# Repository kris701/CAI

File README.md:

# Centralised Auxiliary Interface (CAI)

A project about centralizing a lot of the auxiliary systems for my 3D printer.
As well as add some new systems, like auto-screws, that makes the operation of the printer a lot easier!
It is also designed to be mounted on my [toolhead extension project](https://github.com/kris701/SnapMaker-Toolhead-Extensions).

### Auto-Screws
Automatic screws to take heatbed and toolhead off and on, to make it significantly easier to switch between CNC, Laser engraver and 3D-printer!

### Menu System
Easy to modify menu system, with a rotary push button control.

### Auto-Setup
Single menu item, to setup all thats needed for CNC or 3D print.
Consisting of tightening screws, turning on LED and for 3D printing, turn on the nozzle blower.

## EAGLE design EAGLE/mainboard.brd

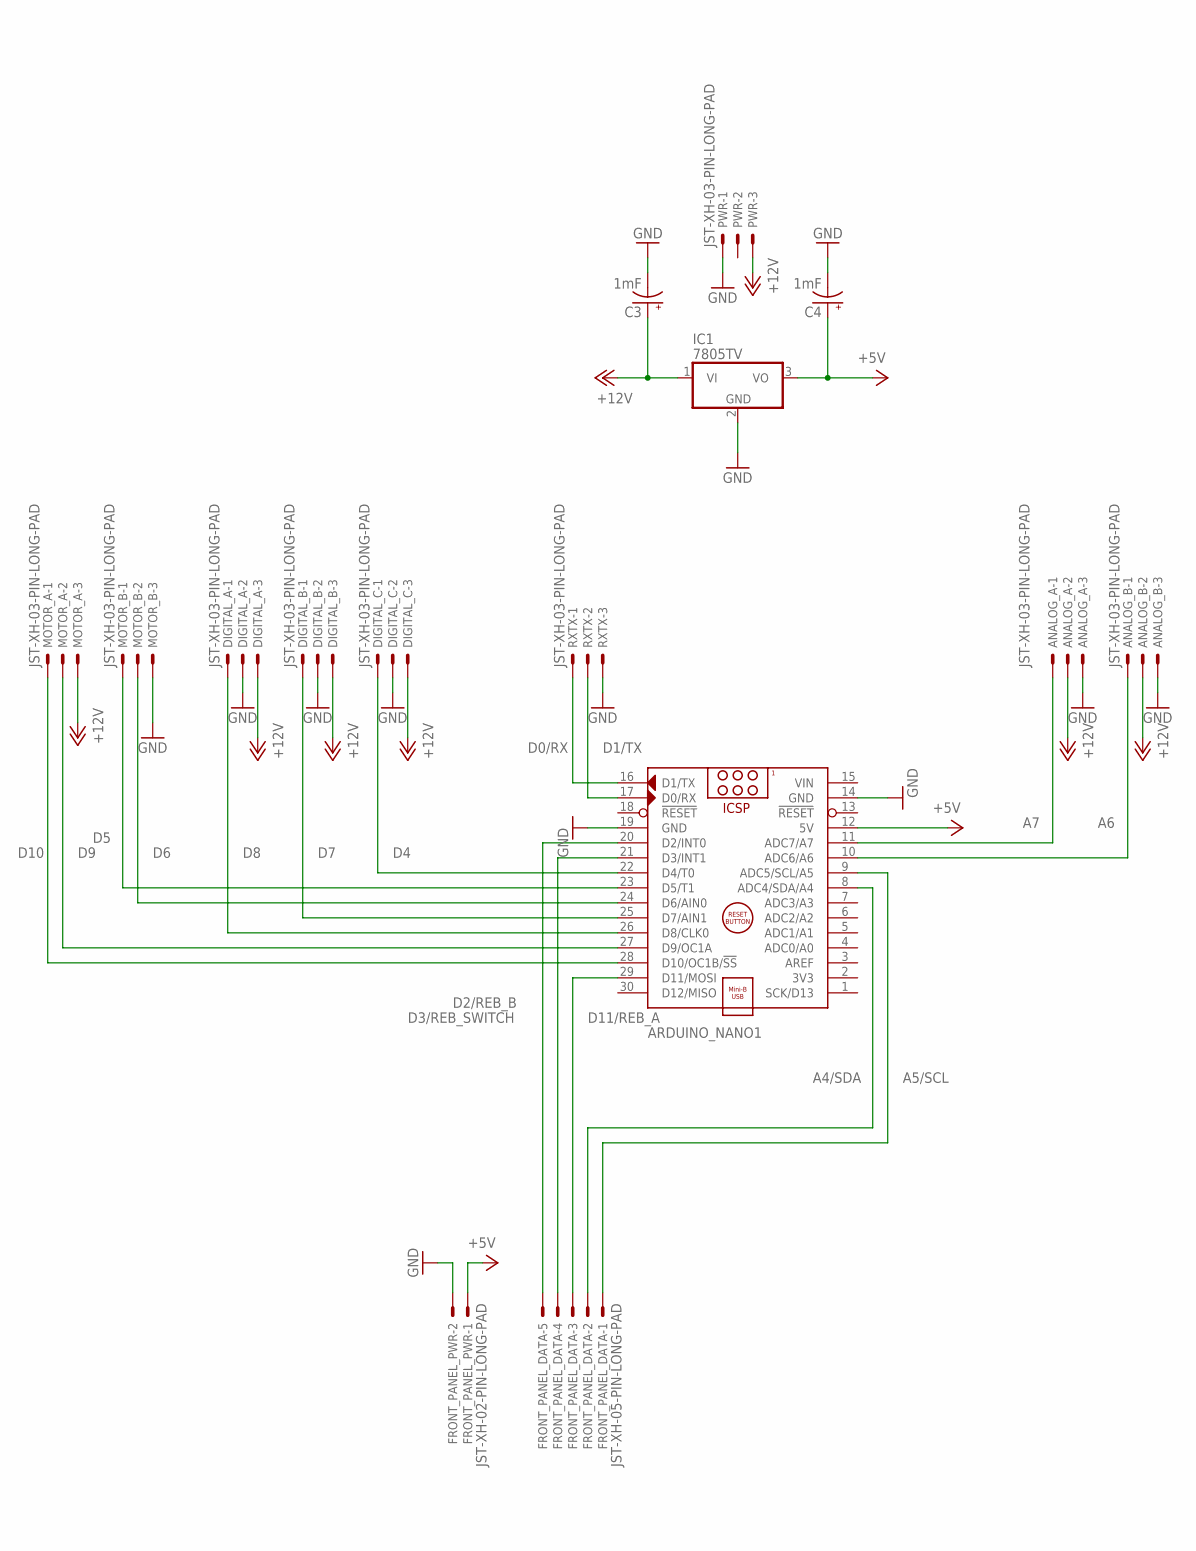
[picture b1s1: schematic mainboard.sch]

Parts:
ANALOG_A: JST-XH-03-PIN-LONG-PAD; JST-XH-03-PACKAGE-LONG-PAD
ANALOG_B: JST-XH-03-PIN-LONG-PAD; JST-XH-03-PACKAGE-LONG-PAD
ARDUINO_NANO1: ARDUINO_NANO
C3, C4: 1mF; CPOL-RADIAL-5MM-10MM
DIGITAL_A: JST-XH-03-PIN-LONG-PAD; JST-XH-03-PACKAGE-LONG-PAD
DIGITAL_B: JST-XH-03-PIN-LONG-PAD; JST-XH-03-PACKAGE-LONG-PAD
DIGITAL_C: JST-XH-03-PIN-LONG-PAD; JST-XH-03-PACKAGE-LONG-PAD
FRONT_PANEL_DATA: JST-XH-05-PIN-LONG-PAD; JST-XH-05-PACKAGE-LONG-PAD
FRONT_PANEL_PWR: JST-XH-02-PIN-LONG-PAD; JST-XH-02-PACKAGE-LONG-PAD
IC1: 7805TV; TO220V
MOTOR_A: JST-XH-03-PIN-LONG-PAD; JST-XH-03-PACKAGE-LONG-PAD
MOTOR_B: JST-XH-03-PIN-LONG-PAD; JST-XH-03-PACKAGE-LONG-PAD
PWR: JST-XH-03-PIN-LONG-PAD; JST-XH-03-PACKAGE-LONG-PAD
RXTX: JST-XH-03-PIN-LONG-PAD; JST-XH-03-PACKAGE-LONG-PAD

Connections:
+5V: ARDUINO_NANO1.12 (5V), C4.+, FRONT_PANEL_PWR.1, IC1.3 (VO)
+12V: ANALOG_A.2, ANALOG_B.2, C3.+, DIGITAL_A.3, DIGITAL_B.3, DIGITAL_C.3, IC1.1 (VI), MOTOR_A.3, PWR.3
A4/SDA: ARDUINO_NANO1.8 (ADC4/SDA/A4), FRONT_PANEL_DATA.2
A5/SCL: ARDUINO_NANO1.9 (ADC5/SCL/A5), FRONT_PANEL_DATA.1
A6: ANALOG_B.1, ARDUINO_NANO1.10 (ADC6/A6)
A7: ANALOG_A.1, ARDUINO_NANO1.11 (ADC7/A7)
D0/RX: ARDUINO_NANO1.17 (D0/RX), RXTX.2
D1/TX: ARDUINO_NANO1.16 (D1/TX), RXTX.1
D2/REB_B: ARDUINO_NANO1.20 (D2/INT0), FRONT_PANEL_DATA.5
D3/REB_SWITCH: ARDUINO_NANO1.21 (D3/INT1), FRONT_PANEL_DATA.4
D4: ARDUINO_NANO1.22 (D4/T0), DIGITAL_C.1
D5: ARDUINO_NANO1.23 (D5/T1), MOTOR_B.1
D6: ARDUINO_NANO1.24 (D6/AIN0), MOTOR_B.2
D7: ARDUINO_NANO1.25 (D7/AIN1), DIGITAL_B.1
D8: ARDUINO_NANO1.26 (D8/CLK0), DIGITAL_A.1
D9: ARDUINO_NANO1.27 (D9/OC1A), MOTOR_A.2
D10: ARDUINO_NANO1.28 (D10/OC1B/!SS), MOTOR_A.1
D11/REB_A: ARDUINO_NANO1.29 (D11/MOSI), FRONT_PANEL_DATA.3
GND: ANALOG_A.3, ANALOG_B.3, ARDUINO_NANO1.14 (GND), ARDUINO_NANO1.19 (GND), C3.-, C4.-, DIGITAL_A.2, DIGITAL_B.2, DIGITAL_C.2, FRONT_PANEL_PWR.2, IC1.2 (GND), MOTOR_B.3, PWR.1, RXTX.3
VIN: ARDUINO_NANO1.15 (VIN)

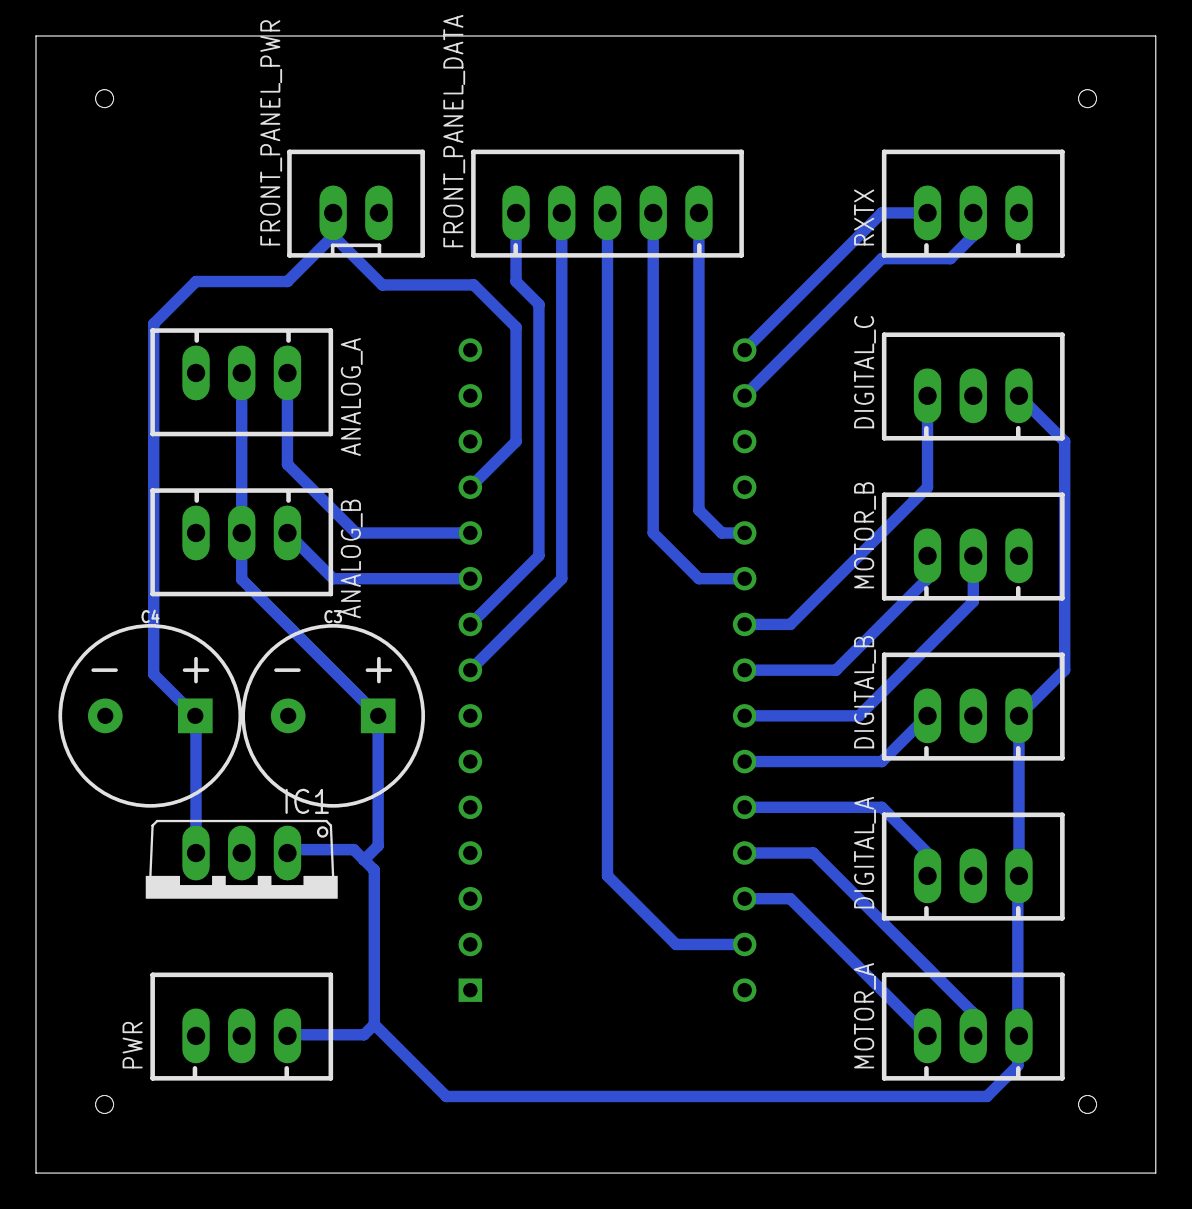
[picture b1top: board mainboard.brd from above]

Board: 2 copper layers, 62.2 x 63.2 mm, 15 parts (1 on the bottom side), 19 nets.

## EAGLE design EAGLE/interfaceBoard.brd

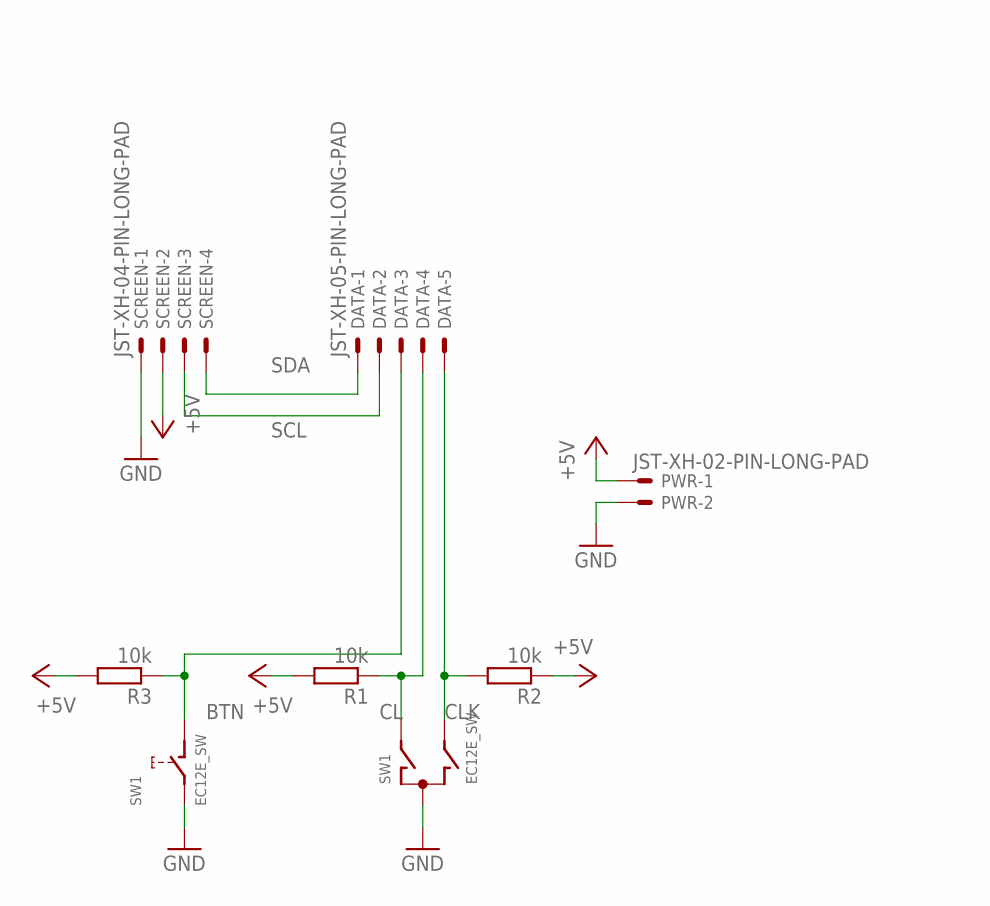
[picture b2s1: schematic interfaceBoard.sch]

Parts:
DATA: JST-XH-05-PIN-LONG-PAD; JST-XH-05-PACKAGE-LONG-PAD
PWR: JST-XH-02-PIN-LONG-PAD; JST-XH-02-PACKAGE-LONG-PAD
R1, R2, R3: 10k; 0204/7
SCREEN: JST-XH-04-PIN-LONG-PAD; JST-XH-04-PACKAGE-LONG-PAD
SW1: EC12E_SW; ALPS_EC12E_SW

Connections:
+5V: PWR.1, R1.2, R2.1, R3.2, SCREEN.2
BTN: DATA.3, R3.1, SW1.D (1)
CL: DATA.4, R1.1, SW1.A
CLK: DATA.5, R2.2, SW1.B
GND: PWR.2, SCREEN.1, SW1.C, SW1.E (2)
SCL: DATA.2, SCREEN.3
SDA: DATA.1, SCREEN.4

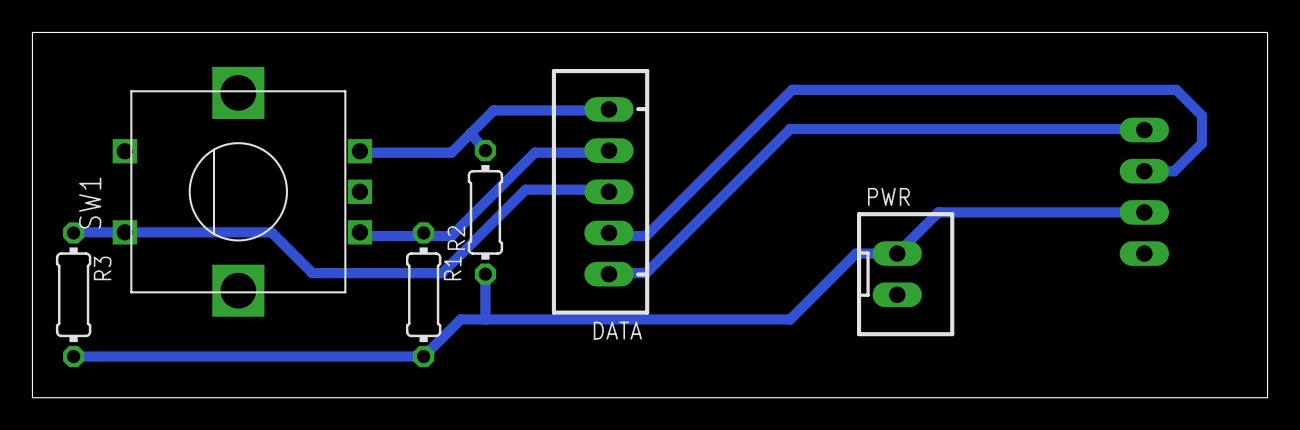
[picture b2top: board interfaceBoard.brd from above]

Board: 2 copper layers, 76.2 x 22.5 mm, 7 parts (1 on the bottom side), 7 nets.

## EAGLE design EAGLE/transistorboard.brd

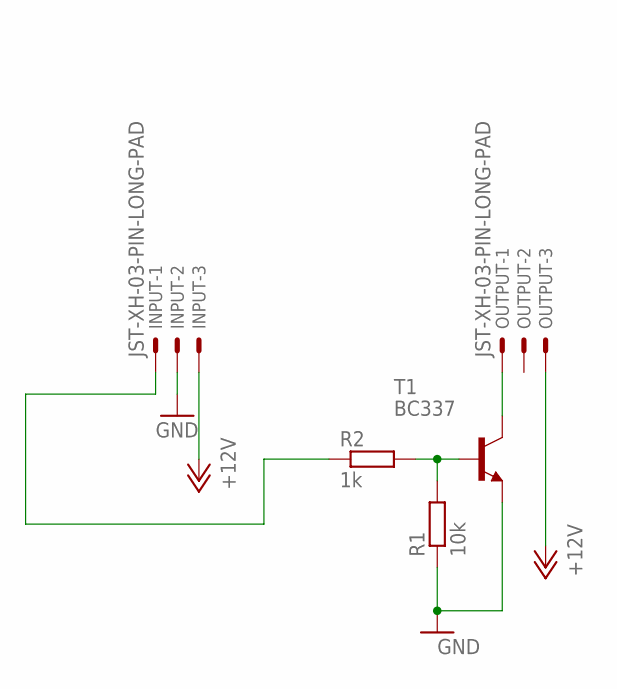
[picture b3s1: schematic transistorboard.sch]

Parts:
INPUT: JST-XH-03-PIN-LONG-PAD; JST-XH-03-PACKAGE-LONG-PAD
OUTPUT: JST-XH-03-PIN-LONG-PAD; JST-XH-03-PACKAGE-LONG-PAD
R1: 10k; 0204/7
R2: 1k; 0204/7
T1: BC337; TO92

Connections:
+12V: INPUT.3, OUTPUT.3
GND: INPUT.2, R1.1, T1.1 (E)
unnamed: OUTPUT.1, T1.3 (C)
unnamed: INPUT.1, R2.1
unnamed: R1.2, R2.2, T1.2 (B)

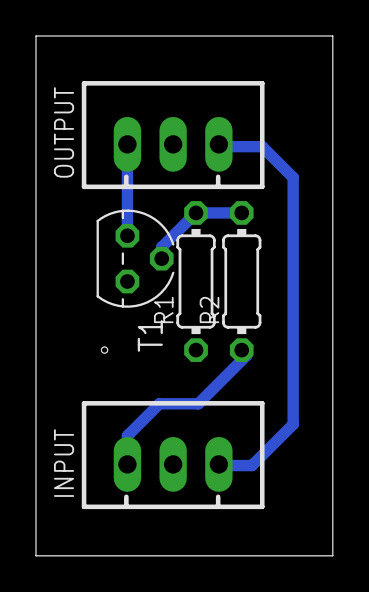
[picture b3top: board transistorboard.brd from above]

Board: 2 copper layers, 16.5 x 28.9 mm, 5 parts (0 on the bottom side), 5 nets.

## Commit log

2021-03-04 Add .gitignore and .gitattributes.
2021-03-04 Add project files.
2021-03-04 * Purged .ino file to default
2021-03-05 * got a basic menu structure to work
2021-03-05 * Removed `String` reference, and uses `const char*` instead
2021-03-05 * big purge * sub menus with sub menues possible * simpler to add new menu items
2021-03-05 * Split the program back out into some classes
2021-03-05 * Cleaned up * Added the systems needed to display text on the OLED screen * Added IO drivers for future modules
2021-03-05 * Removed unused files * Optimised some data types * Made a macro, to switch serial on and off
2021-03-05 * Did some cleanup
2021-03-05 * Added the board schematics for the PCB boards
2021-03-06 * Added definitions for available pins
2021-03-06 * Fixed issue #1 * Also added some more serial debugging
2021-03-08 * Saved a small bit of memory in the `menuTree`
2021-03-08 * Further reduced memory usage, with PROGMEM * Added some default text strings that can be used, such as "ON" and "OFF"
2021-03-08 * Added a delay in loop, so not to waste too much power
2021-03-08 * Made a lot of methods use constants instead
2021-03-08 * Added a lot of classes to be able to set things to private and public
2021-03-08 * Made more classification
2021-03-09 * Made a configuration section * Changed the DD designation in CAI.h to just numbers
2021-03-10 * Changed the rotary encoder code, to match that of the following source: - https://www.instructables.com/Tutorial-of-Rotary-Encoder-With-Arduino/ * Changed boards and schematic, so that interrupt pi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
2021-03-10 * Changed symbolic constants to fit mother board * Removed function pointers from the `RotaryButtonDriver` class, since they are not used * Added pinModes for all pins used for the Rotary Button
2021-03-10 * Made some minor changes on the motherboard, so that the +5v rail is connected to +5v on the arduino instead of vin
2021-03-10 * Optimised the motherboard a little
2021-03-10 * Added some "pseudo-properties" somewhat like C# with macros
2021-03-11 * Moved all EAGLE files into the project * Removed old copy-pasted boards * Updated .gitignore
2021-03-11 * Now gives a warning when compiling with SERIAL_PRINT to be true
2021-03-11 * Made some more work with properties * Made two classes in ModuleDrivers instead of just one * Fixed an issue, where the "SET" methods of properties didnt work * Made some initial checking on valid 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
2021-03-12 * Made some value checking * Also added a flag `SERIAL_DEBUG` to print errors that arrise from `Set` methods
2021-03-12 * Removed unused `this->` statements
2021-03-12 * Cleaned up and fixed the macro `CHECKVALUE`
2021-03-16 * Fixed code so it works with the SH1106 chip * Made initial menu work * Removed serial on warning * Now uses significantly less memory from new library
2021-03-16 * Updated some getters * Updated the intro screen
2021-03-17 * Made the entire screen refreshing sequence a lot more smooth * Added some more structured rectangle controls, to make it easier to allign items * Made a highlight animation when a button is clicked
2021-03-17 * Updated the `EnterMenu()` method * Removed unused define
2021-03-17 * Made the enter menu highlighting faster
2021-03-17 * Removed buffer
2021-03-17 * Removed the Get and Set structure
2021-03-17 * Did a lot of optimization of the menu rendering
2021-03-17 * Took care of issue #2 - Configuration of different systems have been put in a seperate file and header
2021-03-18 * Moved some constant values outside of the ScreenDriver class
2021-03-18 * Added a few constant modifiers around the place
2021-05-05 * Added all the current 3D design files (Fusion files) * Added the Mk. 2 version of the transistor board, that mounts on the toolhead
2021-05-08 * Added a LED holder for a little LED strip * Updated the transistor module mk II * Updated the back extension plate to mk. II
2021-05-11 * Got the rotatry encoder, so now the code works with it
2021-05-12 * Removed the need for interrupts, uses a Tick logic instead
2021-05-13 * Designed an interface board
2021-05-14 * Small fix where the +5v and GND rail was reversed to the LCD screen on the interface board
2021-05-17 * Fixed a small bug in the dual module driver * Updated the mainboard
2021-06-17 * Added new Interface module case fusion files
2021-07-10 * Made the menu correct, with all the items thats actually on the machine
2021-07-10 * Added a missing `pinMode()` to the `ModuleDriver` constructor * Updates the transistor module mk 2 model * Added a new screw module * Updated the main board case to a Mk. 2 variant
2021-07-10 * Small change in the transistor module Mk. 2, so that they can be "stacked" in series if needed
2021-07-12 * Fixed the rotation direction of the screw code * Removed the `turnFANON()` call from the `basecnc()` function * Updated the front panel, to include the name of the project, and a nob to turn with
2021-07-12 * Moved code into a "code" folder
2021-07-13 * Updated the interface board, to include the module name on the side * Also made the knob a little lower profile
2021-07-13 * Updated the knob for the interface board again * Added a wire holder, for cable management * Increased the screw/unscrew time for the screw modules, and made it as a variable that can be changed
2021-07-13 * Made sure that the cursor dont move back to the top, when returning from a menu * Also made sure that the cursor wont move when doing a command
2021-07-16 * Added a "hold" option for dual motor drivers, so that to make sure that they stay in place under a print
2021-12-08 Bumped code versions to work with VS2022
2021-12-27 * Added print settings * Added STL files * Removed old design files

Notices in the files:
parts and their libraries:
SparkFun-Capacitors: Licensing: Creative Commons ShareAlike 4.0 International - https://creativecommons.org/licenses/by-sa/4.0
